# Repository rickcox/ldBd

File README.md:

# ldBd
Simple Load Board for Power Supply Testing

This is a very simple PCB design to act as a power supply load board.  
Yes, there are fancy load boards available out there with digital readouts, fans, etc.
This goes opposite that - it is ***trivially simple***.
This is a simple 2 sided PCB 100mm X 100mm with 50 and 25 watt power resistors that can
be connected various ways using banana plug jumpers.
(See notes on the back of the PCB for some options)

It's a bit of a squeeze getting everything to fit, but staying at 100mmX100mm keeps board manufacturing inexpensive.
You can have bare PCB's fabricated for you very inexpensively.
(For example I paid $2.00 + shipping for 5 bare boards from https://jlcpcb.com)

The files needed for PCB manufacturing are in the 'gerbers/'
directory.  The design was done in KiCad version 7, and the files with extensions "kicad_*" can be used to
modify it further, if you wish.

The power resistors are connected to the board mounting holes via short soldered jumpers and M3 bolts/nuts.
The whole top and bottom surfaces are mostly big copper pours, so resistor heat is spread across the entire board.

I haven't generated an official BOM, but the parts list is fairly simple:

- R1 is a 4 ohm, 50 watt power resistor
- R2 is a 2 ohm, 50 watt power resistor
- R3 is a 1 ohm, 50 watt power resistor
- R4 is a 0.5 ohm, 25 watt power resistor
- J1-17 (17 items) are banana jacks. I used black on one side and red on the other, but .. whatever you want.
- If you want the current sense option, J18 is a 1X2 0.1" pin header, and R5 is a 0.002 ohm 1206 sized surface mount resistor. Both are easy to hand solder.
- You will also need some M3 bolts&nuts - or similar - to hold the resistors down.
- and of course you need to make or buy banana plug jumpers.

Talking about parts; I am US based. The load resistors are available at reasonable prices from most any electronics
distributor - Digikey, Mouser, Newark, etc.  However, the only place I could find banana jacks
and plugs at a reasonable price (I don't consider > $1 each to be reasonable) was from China.
The jacks&plugs I used were from AliExpress - and YES as you can see if you look closely at the next picture - 
*the same supplier gave me 2 different styles*!

I 3d printed a simple base for the board.  The stl file for that is in the 'case/' directory. Use M3 bolts to fasten the board down.
Since the board CAN get quite warm, PETG or an alternate material with a higher glass transition temperature than PLA is recommended.

And here's ***my*** finished product!

Usage is simple - you need to know `e = i * r` and how to calculate effective parallel and series resistances.
(Again, see the notes on the back of the board for some ideas)

Also - ***Use common sense***. Do not exceed the resistor ratings! I have found dissipating even 20 watts continuously
for 5-10 minutes on this board can make it get very warm. Use a fan if needed to increase heat transfer.

This work is licensed under the Creative Commons Attribution 4.0 International License. To view a copy of the license, visit https://creativecommons.org/licenses/by/4.0/

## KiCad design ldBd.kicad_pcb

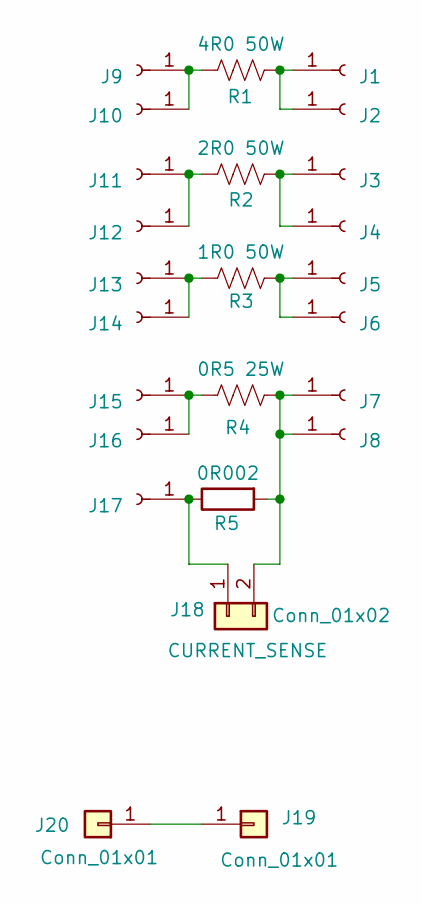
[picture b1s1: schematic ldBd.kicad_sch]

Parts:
J1, J2, J3, J4, J5, J6, J7, J8, J9, J10, J11, J12, J13, J14, J15, J16, J17: Conn_01x01_Female; Banana_Jack_1Pin
J18: Conn_01x02; PinHeader_1x02_P2.54mm_Vertical
J19, J20: Conn_01x01; PinHeader_1x01_P2.54mm_Vertical
R1: 4R0 50W; R_POWER_50W
R2: 2R0 50W; R_POWER_50W
R3: 1R0 50W; R_POWER_50W
R4: 0R5 25W; R_POWER_25W
R5: 0R002; R_1206_3216Metric

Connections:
unnamed: J1.1, J2.1, R1.2
unnamed: J3.1, J4.1, R2.2
unnamed: J5.1, J6.1, R3.2
unnamed: J9.1, J10.1, R1.1
unnamed: J11.1, J12.1, R2.1
unnamed: J13.1, J14.1, R3.1
unnamed: J15.1, J16.1, R4.1
unnamed: J17.1, J18.1, R5.1
unnamed: J7.1, J8.1, J18.2, R4.2, R5.2
unnamed: J19.1, J20.1

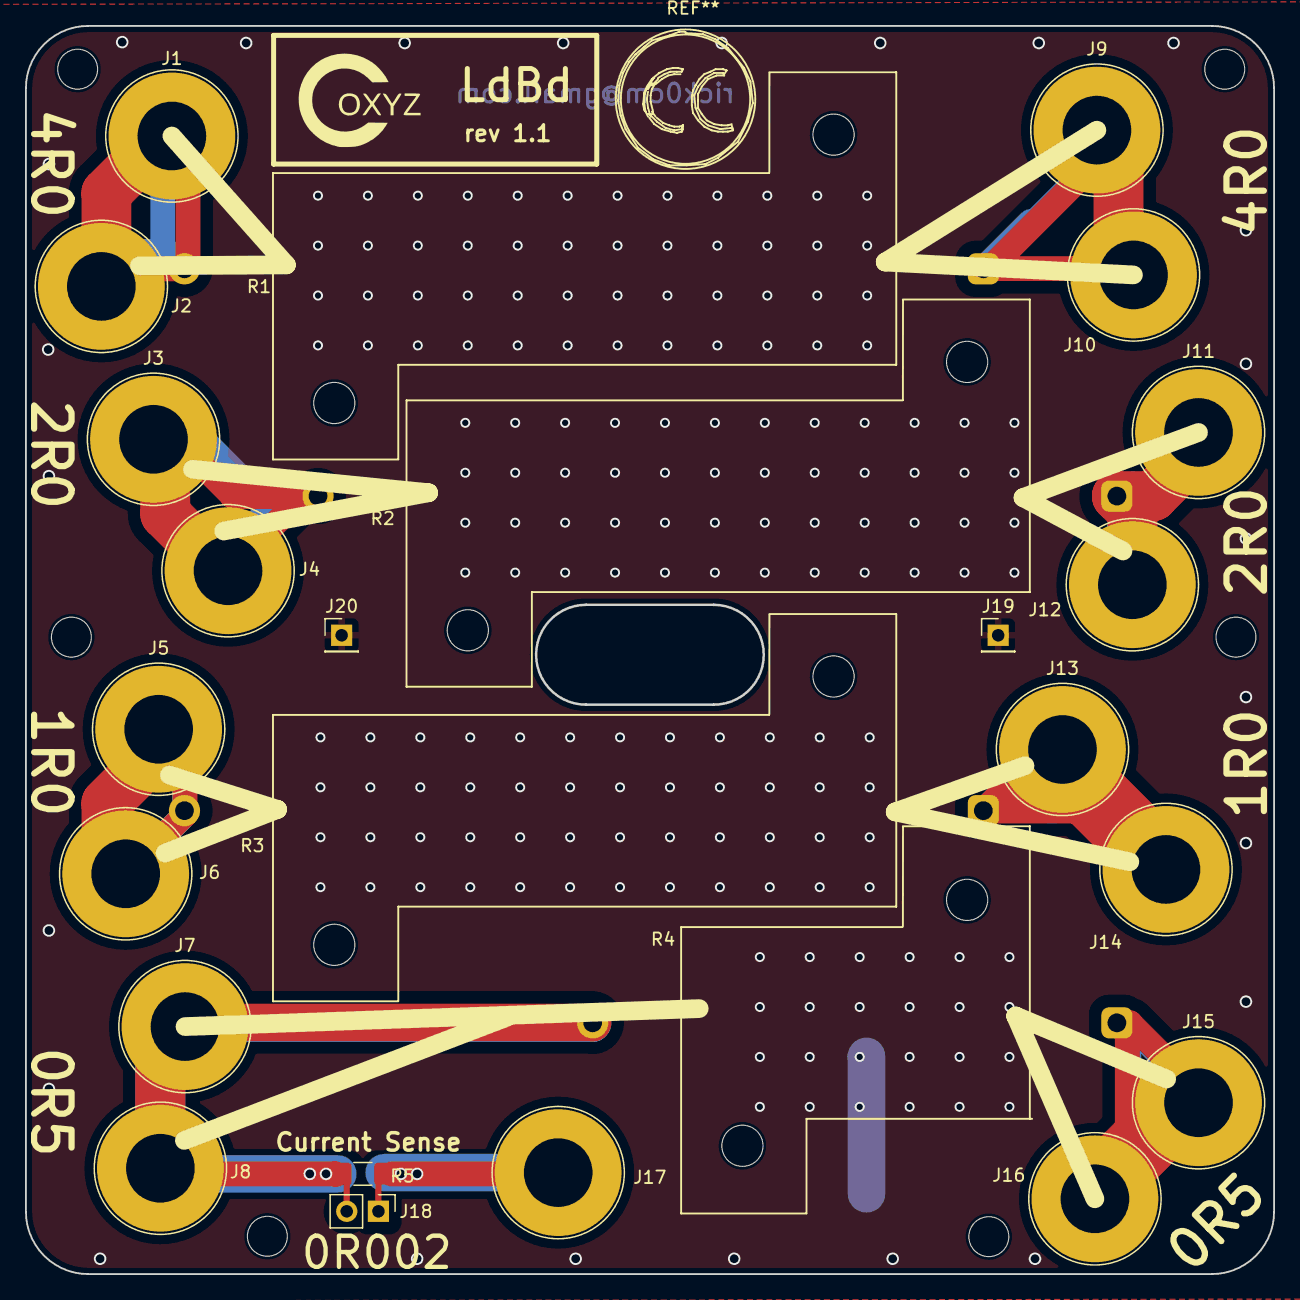
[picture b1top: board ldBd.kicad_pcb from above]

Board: 2 copper layers, 100.0 x 100.0 mm, 25 parts (0 on the bottom side), 10 nets.

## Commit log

2023-03-17 Update README.md
    Fix a typo
2023-03-17 initial push
2023-03-17 Fixed typos
2023-03-17 Crop images down to size
2023-03-17 Added usage note
2023-03-17 Add schematic
2023-03-17 Modify usage note
2023-03-17 Cleanup text
2023-03-30 Add pointer to pcb back

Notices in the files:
ldBd.kicad_pcb:
This work is licensed under a Creative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
